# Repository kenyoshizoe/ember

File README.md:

# Ember
## Overview
32Key Hall Effect Keyboard for Gaming.

## Web Configuration Tool

Meet Ember’s control room in the browser. The Next.js‑powered configurator lets you:

- Configuring keymaps with instant write-backs over Web Serial
- Watch real-time hall-effect telemetry and dial in rapid trigger thresholds
- Fire off calibration, DFU, and other maintenance commands in a single click

Launch (Chrome / Edge recommended):
https://ember.kenyo.dev

https://x.com/m3ssy_ken/status/1974076255810269626

## PCB
pcb/ember

基板はKiCAD7で制作され、USBコネクタを除く全てのパーツはJLCPCBのPCBAサービスで実装することができます。
TypeCコネクタは[5077CR-16-SMC2-BK-TR](https://akizukidenshi.com/catalog/g/gC-14356/)を用いることができます。

pcb was designed with KiCAD 7.
All of components except USB Connector is available at jlcpcb pcba service.

## Case
pcb/ember_bottom_plate, pcb/ember_top_plate

## Communication
このキーボードはHID&CDC複合デバイスとして認識されます。
各種設定はCDCから行うことができます。

This keyboard is recognized as HID&CDC composite device.
Configuration (Keymapping, Calibration, Rapid Trigger, etc...) can be done from CDC.

### Packet Structure
Query (Read)
| Bytes     | Description |
| --------- | ----------- |
| 0x00      | 0           |
| 0x01~0x02 | Address     |
| 0x03      | Length      |

Response (Read)
| Bytes           | Description        |
| --------------- | ------------------ |
| 0x00            | Success=0 Failed=1 |
| 0x01~0x02       | Address            |
| 0x03            | Length             |
| 0x04~(Length+4) | Data               |

Query (Write)
| Bytes           | Description |
| --------------- | ----------- |
| 0x00            | 1           |
| 0x01~0x02       | Address     |
| 0x03            | Length      |
| 0x04~(Length+4) | Data        |

Response (Write)
| Bytes     | Description        |
| --------- | ------------------ |
| 0x00      | Success=0 Failed=1 |
| 0x01~0x02 | Address            |
| 0x03      | Length             |

これらのクエリ/レスポンスをCOBSを用いてエンコード/デコードしてから送受信します。
Send these query with encoding/decoding with COBS.

### Address Map
| Address       | Description                                        | W/R |
| ------------- | -------------------------------------------------- | --- |
| 0x0000-0x0004 | Key0 Config                                        | W/R |
| 0x0005-0x0009 | Key1 Config                                        | W/R |
| 0x000A-0x000E | Key2 Config                                        | W/R |
| ...           | ...                                                | ... |
| 0x009B-0x009F | Key31 Config                                       | W/R |
| 0x00A0-0x00FF | Reserved                                           | -   |
| 0x0100        | Key1 MIDI Note Number                              | W/R |
| 0x0101        | Key2 MIDI Note Number                              | W/R |
| 0x0102        | Key3 MIDI Note Number                              | W/R |
| ...           | ...                                                | ... |
| 0x0120-0x0FFF | Reserved                                           | -   |
| 0x1000-0x1003 | Key0 Calibaration Data                             | R   |
| 0x1004-0x1007 | Key1 Calibaration Data                             | R   |
| ...           | ...                                                | ... |
| 0x107B-0x107F | Key31 Calibration Data                             | R   |
| 0x1080-0x1FFF | Reserved                                           | -   |
| 0x2000        | Key0 Push distance                                 | R   |
| 0x2001        | Key1 Push distance                                 | R   |
| ...           | ...                                                | ... |
| 0x201F        | Key31 Push distance                                | R   |
| 0x2020-0x2FFF | Reserved                                           | -   |
| 0x3000        | Save Config                                        | W   |
| 0x3001        | Calibration (0=Disable 1=Enable)                   | W   |
| 0x3002        | Reset Config to default                            | W   |
| 0x3003        | Reset MCU                                          | W   |
| 0x3004        | Enter DFU                                          | W   |
| 0x3005-0xFFFF | Reserved                                           | -   |
| 0x4000        | Mode (0=DISABLED, 1=CALIBRATE, 2=KEYBAORD, 3=MIDI) | W/R |

それぞれのキーの設定は次のようになっています。
Each key config is as follows:
| Address | Description                                                      |
| ------- | ---------------------------------------------------------------- |
| 0x00    | key_code                                                         |
| 0x01    | key_type (0=DISABLED, 1=CALIBRATE, 2=THRESHOLD, 3=RAPID_TRIGGER) |
| 0x02    | actuation_point (0.1mm unit)                                     |
| 0x03    | rappid_trigger_up_sensivity                                      |
| 0x04    | rappid_trigger_down_sensivity                                    |

それぞれのキーのキャリブレーションデータは以下のようになっています。
Each key calibration data is as follows:
| Address   | Description |
| --------- | ----------- |
| 0x00~0x01 | max_value   |
| 0x02~0x03 | min_value   |

## License

Unless otherwise noted, all original content in this repository—including the
firmware, web configurator, scripts, PCB design files, schematics, and case
design files—is licensed under the [MIT License](LICENSE).

This includes permission to use the design files to manufacture, distribute,
and sell physical products based on those designs.

Third-party components remain subject to their respective licenses.

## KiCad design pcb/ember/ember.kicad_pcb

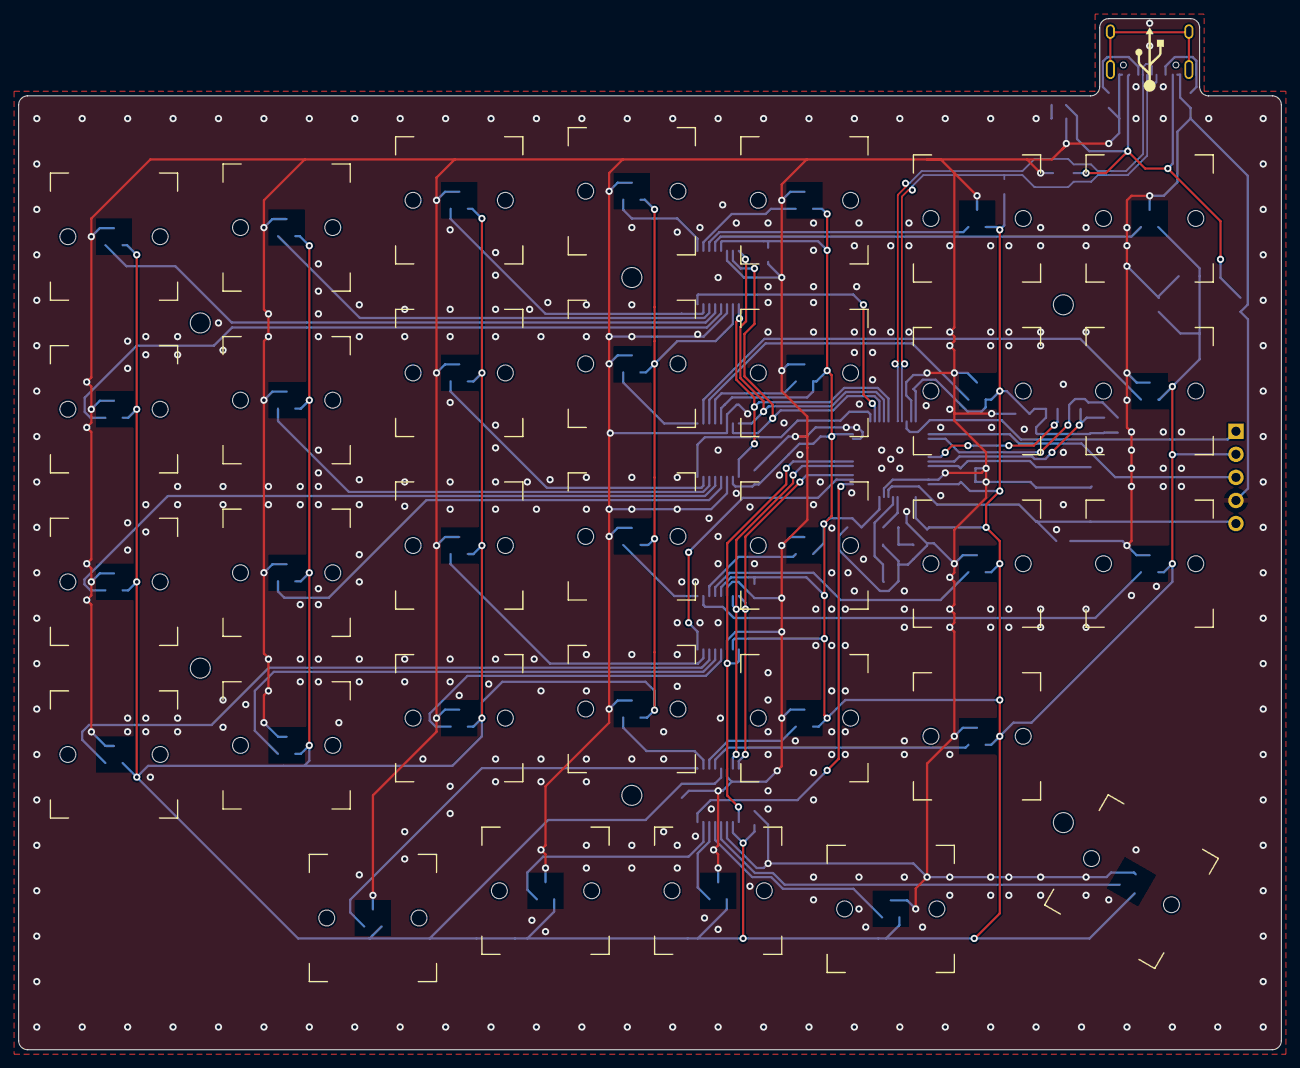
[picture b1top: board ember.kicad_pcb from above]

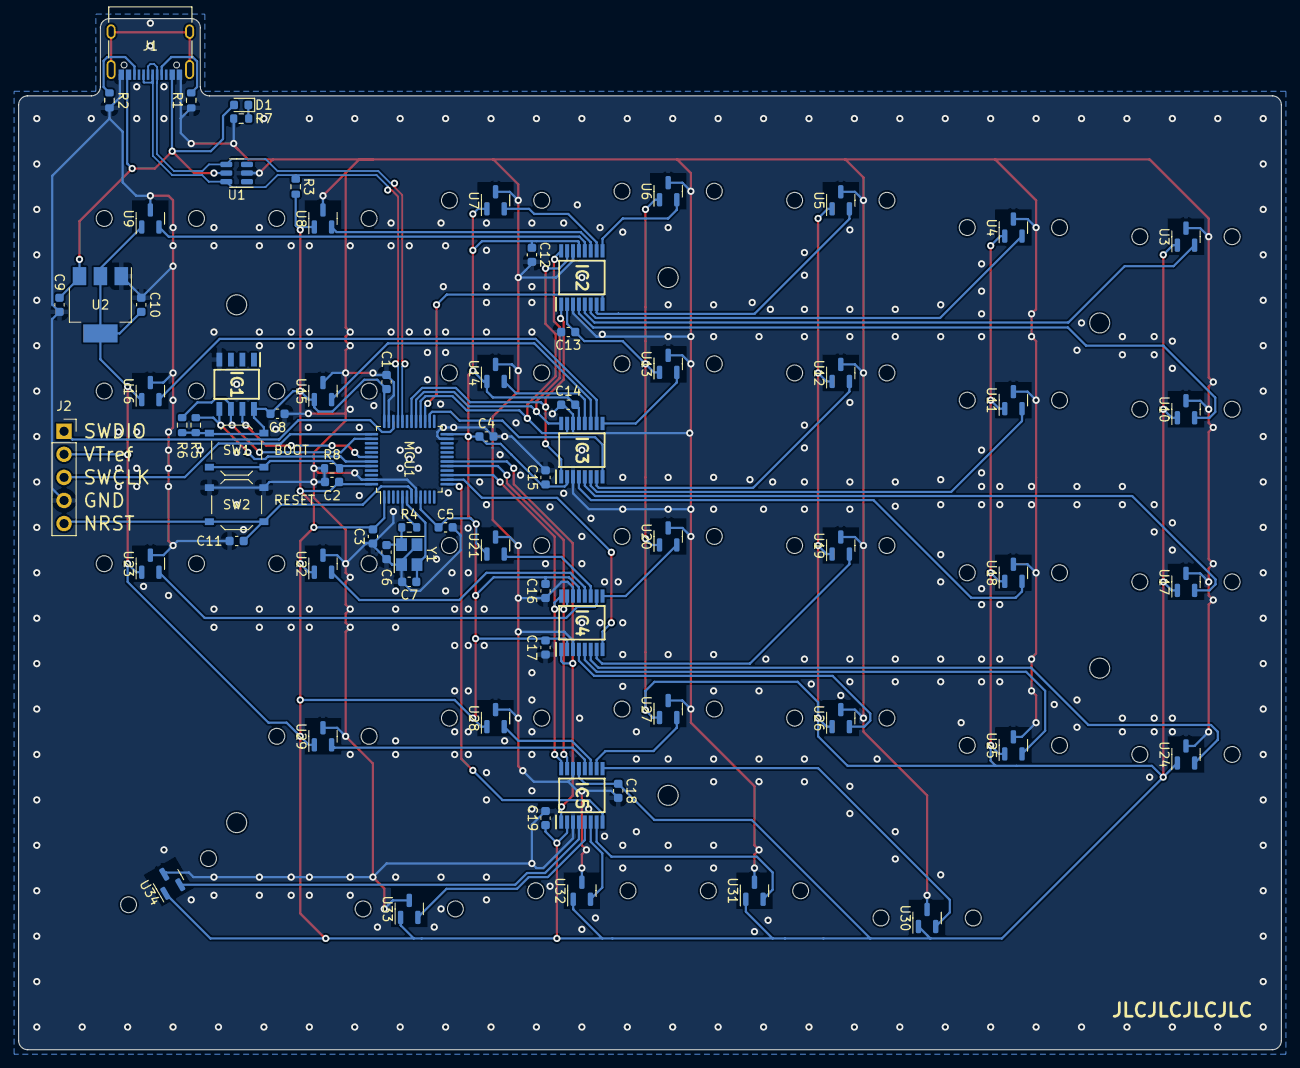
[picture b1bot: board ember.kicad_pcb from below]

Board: 2 copper layers, 139.0 x 113.5 mm, 111 parts (73 on the bottom side), 60 nets.

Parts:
C1, C2, C3, C4, C8, C11, C12, C13, C14, C15, C16, C17, C18, C19: 100n; C_0603_1608Metric
C5: 10n; C_0603_1608Metric
C6, C7: 10p; C_0603_1608Metric
C9: 10u; C_0603_1608Metric
C10: 22u; C_0603_1608Metric
D1: LED; LED_0603_1608Metric
H1, H2, H3, H4, H5, H6: MountingHole; MountingHole_2.2mm_M2
H7, H8, H9, H10, H11, H12, H13, H14, H15, H16, H17, H18, H19, H20, H21, H22, H23, H24, H25, H26, H27, H28, H29, H30, H31, H32, H33, H34, H35, H36, H37, H38: KeySwitch; MX-1U-NoPins
IC1: M24C64-RMN6TP; SOIC127P600X175-8N
IC2, IC3, IC4, IC5: ADG708BRUZ-REEL7; SOP65P640X120-16N
J1: USB_C_Receptacle_USB2.0; USB_C_Receptacle_XKB_U262-16XN-4BVC11
J2: Conn_01x05_Socket; PinSocket_1x05_P2.54mm_Vertical
MCU1: STM32F303CBTx; LQFP-48_7x7mm_P0.5mm
R1, R2: 5.1k; R_0603_1608Metric
R3: 1.5k; R_0603_1608Metric
R4, R8: 1k; R_0603_1608Metric
R5, R6: 10k; R_0603_1608Metric
R7: 470; R_0603_1608Metric
SW1: BOOT; SW_Push_1P1T_XKB_TS-1187A
SW2: RESET; SW_Push_1P1T_XKB_TS-1187A
U1: SRV05-4; SOT-23-6
U2: AMS1117-3.3; SOT-223-3_TabPin2
U3, U4, U5, U6, U7, U8, U9, U10, U11, U12, U13, U14, U15, U16, U17, U18, U19, U20, U21, U22, U23, U24, U25, U26, U27, U28, U29, U30, U31, U32, U33, U34: Hall_Sensor; SOT-23
Y1: 16MHz; Crystal_SMD_3225-4Pin_3.2x2.5mm

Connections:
+3.3V: C1.1, C2.1, C3.1, C4.1, C5.1, C8.1, C10.1, C12.1, C13.1, C14.1, C15.1, C16.1, C17.1, C18.1, C19.1, IC1.8 (VCC), IC2.2 (EN), IC2.13 (VDD), IC3.2 (EN), IC3.13 (VDD), IC4.2 (EN), IC4.13 (VDD), IC5.2 (EN), IC5.13 (VDD), J2.2, MCU1.1 (VBAT), MCU1.9 (VDDA), MCU1.24 (VDD), MCU1.36 (VDD), MCU1.48 (VDD), R3.2, R5.1, R6.1, SW1.2, U2.2 (VO), U3.1 (VDD), U4.1 (VDD), U5.1 (VDD), U6.1 (VDD), U7.1 (VDD), U8.1 (VDD), U9.1 (VDD), U10.1 (VDD), U11.1 (VDD), U12.1 (VDD), U13.1 (VDD), U14.1 (VDD), U15.1 (VDD), U16.1 (VDD), U17.1 (VDD), U18.1 (VDD), U19.1 (VDD), U20.1 (VDD), U21.1 (VDD), U22.1 (VDD), U23.1 (VDD), U24.1 (VDD), U25.1 (VDD), U26.1 (VDD), U27.1 (VDD), U28.1 (VDD), U29.1 (VDD), U30.1 (VDD), U31.1 (VDD), U32.1 (VDD), U33.1 (VDD), U34.1 (VDD)
+5V: C9.1, D1.2 (A), J1.A4 (VBUS), J1.A9 (VBUS), J1.B4 (VBUS), J1.B9 (VBUS), U1.5 (VP), U2.3 (VI)
ADC1: IC5.8 (D), MCU1.13 (PA3)
ADC2: IC4.8 (D), MCU1.14 (PA4)
ADC3: IC3.8 (D), MCU1.26 (PB13)
ADC4: IC2.8 (D), MCU1.27 (PB14)
BOOT: MCU1.44 (BOOT0), R8.1, SW1.1
GND: C1.2, C2.2, C3.2, C4.2, C5.2, C6.2, C7.2, C8.2, C9.2, C10.2, C11.2, C12.2, C13.2, C14.2, C15.2, C16.2, C17.2, C18.2, C19.2, IC1.4 (VSS), IC2.3 (VSS), IC2.14 (GND), IC3.3 (VSS), IC3.14 (GND), IC4.3 (VSS), IC4.14 (GND), IC5.3 (VSS), IC5.14 (GND), J1.A1 (GND), J1.A12 (GND), J1.B1 (GND), J1.B12 (GND), J2.4, MCU1.8 (VSSA), MCU1.23 (VSS), MCU1.35 (VSS), MCU1.47 (VSS), R1.2, R2.2, R7.2, R8.2, SW2.2, U1.2 (VN), U2.1 (GND), U3.3 (GND), U4.3 (GND), U5.3 (GND), U6.3 (GND), U7.3 (GND), U8.3 (GND), U9.3 (GND), U10.3 (GND), U11.3 (GND), U12.3 (GND), U13.3 (GND), U14.3 (GND), U15.3 (GND), U16.3 (GND), U17.3 (GND), U18.3 (GND), U19.3 (GND), U20.3 (GND), U21.3 (GND), U22.3 (GND), U23.3 (GND), U24.3 (GND), U25.3 (GND), U26.3 (GND), U27.3 (GND), U28.3 (GND), U29.3 (GND), U30.3 (GND), U31.3 (GND), U32.3 (GND), U33.3 (GND), U34.3 (GND), Y1.2, Y1.4
MUX1_A: IC4.1 (A0), IC5.1 (A0), MCU1.18 (PB0)
MUX1_B: IC4.16 (A1), IC5.16 (A1), MCU1.15 (PA5)
MUX1_C: IC4.15 (A2), IC5.15 (A2), MCU1.17 (PA7)
MUX2_A: IC2.1 (A0), IC3.1 (A0), MCU1.30 (PA9)
MUX2_B: IC2.16 (A1), IC3.16 (A1), MCU1.29 (PA8)
MUX2_C: IC2.15 (A2), IC3.15 (A2), MCU1.28 (PB15)
NRST: C11.1, J2.5, MCU1.7 (NRST), SW2.1
unnamed: C6.1, R4.1, Y1.1
unnamed: D1.1 (K), R7.1
unnamed: J1.A5 (CC1), R1.1
unnamed: J1.B5 (CC2), R2.1
RCC_OSC_IN: MCU1.5 (PF0), R4.2
RCC_OSC_OUT: C7.1, MCU1.6 (PF1), Y1.3
SCL: IC1.6 (SCL), MCU1.38 (PA15), R6.2
SDA: IC1.5 (SDA), MCU1.43 (PB7), R5.2
SENS_A_S1: IC2.4 (S1), U10.2 (OUT)
SENS_A_S2: IC2.5 (S2), U3.2 (OUT)
SENS_A_S3: IC2.6 (S3), U4.2 (OUT)
SENS_A_S4: IC2.7 (S4), U5.2 (OUT)
SENS_A_S5: IC2.12 (S5), U9.2 (OUT)
SENS_A_S6: IC2.11 (S6), U8.2 (OUT)
SENS_A_S7: IC2.10 (S7), U7.2 (OUT)
SENS_A_S8: IC2.9 (S8), U6.2 (OUT)
SENS_B_S1: IC3.4 (S1), U18.2 (OUT)
SENS_B_S2: IC3.5 (S2), U17.2 (OUT)
SENS_B_S3: IC3.6 (S3), U11.2 (OUT)
SENS_B_S4: IC3.7 (S4), U12.2 (OUT)
SENS_B_S5: IC3.12 (S5), U14.2 (OUT)
SENS_B_S6: IC3.11 (S6), U15.2 (OUT)
SENS_B_S7: IC3.10 (S7), U16.2 (OUT)
SENS_B_S8: IC3.9 (S8), U13.2 (OUT)
SENS_C_S1: IC4.4 (S1), U26.2 (OUT)
SENS_C_S2: IC4.5 (S2), U25.2 (OUT)
SENS_C_S3: IC4.6 (S3), U24.2 (OUT)
SENS_C_S4: IC4.7 (S4), U19.2 (OUT)
SENS_C_S5: IC4.12 (S5), U22.2 (OUT)
SENS_C_S6: IC4.11 (S6), U21.2 (OUT)
SENS_C_S7: IC4.10 (S7), U23.2 (OUT)
SENS_C_S8: IC4.9 (S8), U20.2 (OUT)
SENS_D_S1: IC5.4 (S1), U34.2 (OUT)
SENS_D_S2: IC5.5 (S2), U33.2 (OUT)
SENS_D_S3: IC5.6 (S3), U32.2 (OUT)
SENS_D_S4: IC5.7 (S4), U31.2 (OUT)
SENS_D_S5: IC5.12 (S5), U29.2 (OUT)
SENS_D_S6: IC5.11 (S6), U28.2 (OUT)
SENS_D_S7: IC5.10 (S7), U27.2 (OUT)
SENS_D_S8: IC5.9 (S8), U30.2 (OUT)
SWCLK: J2.3, MCU1.37 (PA14)
SWDIO: J2.1, MCU1.34 (PA13)
USB_D+: J1.A6 (D+), J1.B6 (D+), MCU1.33 (PA12), R3.1, U1.6 (IO4)
USB_D-: J1.A7 (D-), J1.B7 (D-), MCU1.32 (PA11), U1.4 (IO3)
WC: IC1.7 (~WC), MCU1.42 (PB6)

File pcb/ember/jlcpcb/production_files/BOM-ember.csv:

Comment,Designator,Footprint,LCSC
STM32F303CBTx,MCU1,LQFP-48_7x7mm_P0.5mm,C108516
16MHz,Y1,Crystal_SMD_3225-4Pin_3.2x2.5mm,C13738
100n,"C1,C11,C12,C13,C14,C15,C16,C17,C18,C19,C2,C3,C4,C8",C_0603_1608Metric,C14663
10p,"C6,C7",C_0603_1608Metric,C1634
10u,C9,C_0603_1608Metric,C19702
1k,"R4,R8",R_0603_1608Metric,C21190
1.5k,R3,R_0603_1608Metric,C22843
470,R7,R_0603_1608Metric,C23179
5.1k,"R1,R2",R_0603_1608Metric,C23186
10k,"R5,R6",R_0603_1608Metric,C25804
Hall_Sensor,"U10,U11,U12,U13,U14,U15,U16,U17,U18,U19,U20,U21,U22,U23,U24,U25,U26,U27,U28,U29,U3,U30,U31,U32,U33,U34,U4,U5,U6,U7,U8,U9",SOT-23,C2904393
BOOT,"SW1,SW2",SW_Push_1P1T_XKB_TS-1187A,C318884
USB_C_Receptacle_USB2.0,J1,USB_C_Receptacle_XKB_U262-16XN-4BVC11,C319148
ADG708BRUZ-REEL7,"IC2,IC3,IC4,IC5",SOP65P640X120-16N,C35325
10n,C5,C_0603_1608Metric,C57112
22u,C10,C_0603_1608Metric,C59461
AMS1117-3.3,U2,SOT-223-3_TabPin2,C6186
LED,D1,LED_0603_1608Metric,C72043
M24C64-RMN6TP,IC1,SOIC127P600X175-8N,C79988
SRV05-4,U1,SOT-23-6,C85364
KeySwitch,H29,MX-1U-NoPins,
KeySwitch,H17,MX-1U-NoPins,
MountingHole,H3,MountingHole_2.2mm_M2,
KeySwitch,H20,MX-1U-NoPins,
MountingHole,H2,MountingHole_2.2mm_M2,
KeySwitch,H31,MX-1U-NoPins,
KeySwitch,H11,MX-1U-NoPins,
KeySwitch,H19,MX-1U-NoPins,
KeySwitch,H9,MX-1U-NoPins,
KeySwitch,H24,MX-1U-NoPins,
KeySwitch,H21,MX-1U-NoPins,
MountingHole,H1,MountingHole_2.2mm_M2,
KeySwitch,H23,MX-1U-NoPins,
KeySwitch,H10,MX-1U-NoPins,
KeySwitch,H14,MX-1U-NoPins,
KeySwitch,H32,MX-1U-NoPins,
MountingHole,H5,MountingHole_2.2mm_M2,
KeySwitch,H16,MX-1U-NoPins,
KeySwitch,H7,MX-1U-NoPins,
KeySwitch,H13,MX-1U-NoPins,
KeySwitch,H30,MX-1U-NoPins,
KeySwitch,H8,MX-1U-NoPins,
KeySwitch,H15,MX-1U-NoPins,
KeySwitch,H18,MX-1U-NoPins,
KeySwitch,H25,MX-1U-NoPins,
KeySwitch,H26,MX-1U-NoPins,
KeySwitch,H12,MX-1U-NoPins,
MountingHole,H6,MountingHole_2.2mm_M2,
KeySwitch,H27,MX-1U-NoPins,
KeySwitch,H28,MX-1U-NoPins,
MountingHole,H4,MountingHole_2.2mm_M2,
KeySwitch,H22,MX-1U-NoPins,
Conn_01x05_Socket,J2,PinSocket_1x05_P2.54mm_Vertical,
KeySwitch,H38,MX-1U-NoPins,
KeySwitch,H37,MX-1U-NoPins,
KeySwitch,H36,MX-1U-NoPins,
KeySwitch,H35,MX-1U-NoPins,
KeySwitch,H34,MX-1U-NoPins,
KeySwitch,H33,MX-1U-NoPins,

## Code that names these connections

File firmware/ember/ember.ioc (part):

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Mcu.Name=STM32F303C(B-C)Tx
Mcu.Package=LQFP48
Mcu.UserName=STM32F303CBTx
PA11.Mode=Device
PA11.Signal=USB_DM
PA12.Mode=Device
PA12.Signal=USB_DP
PA13.Mode=Serial_Wire
PA13.Signal=SYS_JTMS-SWDIO
PA14.Mode=Serial_Wire
PA14.Signal=SYS_JTCK-SWCLK
PA15.Mode=I2C
PA15.Signal=I2C1_SCL
PA3.Mode=IN4-Single-Ended
PA3.Signal=ADC1_IN4
PA4.Mode=IN1-Single-Ended
PA4.Signal=ADC2_IN1
PA5.GPIOParameters=GPIO_Speed,GPIO_Label
PA5.GPIO_Label=MUX1_B
PA5.GPIO_Speed=GPIO_SPEED_FREQ_HIGH
PA5.Signal=GPIO_Output
PA7.GPIOParameters=GPIO_Speed,GPIO_Label
PA7.GPIO_Label=MUX1_C
PA7.GPIO_Speed=GPIO_SPEED_FREQ_HIGH
PA7.Signal=GPIO_Output
PA8.GPIOParameters=GPIO_Speed,GPIO_Label
PA8.GPIO_Label=MUX2_B
PA8.GPIO_Speed=GPIO_SPEED_FREQ_HIGH
PA8.Signal=GPIO_Output
PA9.GPIOParameters=GPIO_Speed,GPIO_Label
PA9.GPIO_Label=MUX2_A
PA9.GPIO_Speed=GPIO_SPEED_FREQ_HIGH
PA9.Signal=GPIO_Output
PB0.GPIOParameters=GPIO_Speed,GPIO_Label
PB0.GPIO_Label=MUX1_A
PB0.GPIO_Speed=GPIO_SPEED_FREQ_HIGH
PB0.Signal=GPIO_Output
PB13.Mode=IN5-Single-Ended
PB13.Signal=ADC3_IN5
PB14.Mode=IN4-Single-Ended
PB14.Signal=ADC4_IN4
PB15.GPIOParameters=GPIO_Speed,GPIO_Label
PB15.GPIO_Label=MUX2_C
PB15.GPIO_Speed=GPIO_SPEED_FREQ_HIGH
PB15.Signal=GPIO_Output
PB6.GPIOParameters=GPIO_Label
PB6.GPIO_Label=EEPROM_WC
PB6.Signal=GPIO_Output
PB7.Mode=I2C
PB7.Signal=I2C1_SDA
PF0-OSC_IN.Mode=HSE-External-Oscillator
PF0-OSC_IN.Signal=RCC_OSC_IN
PF1-OSC_OUT.Mode=HSE-External-Oscillator
PF1-OSC_OUT.Signal=RCC_OSC_OUT
RCC.HSEPLLFreq_Value=16000000
RCC.HSE_VALUE=16000000
RCC.SYSCLKFreq_VALUE=16000000
RCC.SYSCLKSourceVirtual=RCC_SYSCLKSOURCE_HSE
board=custom

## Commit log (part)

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2023-08-13 :tada: add pcb design
2023-08-13 :wrench: add .gitignore for kicad
2023-08-14 :tada: generate project
2023-08-14 :sparkles: add class for cb4051b
2023-08-14 :sparkles: add c_cpp_properties
2023-08-14 :recycle: entry_point->app
2023-08-14 :bug: fix cb4051b ch_
2023-08-14 :sparkles: add NextCh()
2023-08-14 :sparkles: add CD4051B instance
2023-08-14 :wrench: change adc settings
2023-08-15 :heavy_plus_sign: add tinyusb as submodule
2023-08-15 :wrench: disable USB_DEVICE
2023-08-15 :sparkles: configure makefile to build tinyUSB
2023-08-15 :wrench: enable usb irq
2023-08-15 :sparkles: add tusb_config.h
2023-08-23 :wrench: ver1.1
2023-08-23 :sparkles: add tusb process
2023-08-23 :sparkles: add eeprom
2023-08-23 :wrench: fix tinyusb include in makefile
2023-08-24 :wrench: change usb irq setting
2023-08-24 :heavy_plus_sign: add segger_rtt
2023-08-24 :wrench: configure usb_descriptor/tusb_config
2023-08-24 :sparkles: include segger rtt
2023-08-24 :sparkles: add tusb cdc & hid process
2023-08-24 :sparkles: change hid desc
2023-08-24 :sparkles: clean app
2023-08-24 :bug: add 1.5k pullup to D+
2023-08-24 :wrench: add VTref Pin
2023-08-25 :sparkles: all key adc
2023-08-25 :sparkles: adc all kyes @ 800Hz
2023-08-25 :sparkles: change tim hz
2023-08-25 :tada: add keyboard class
2023-08-25 :tada: add keyswitch class
2023-08-25 :sparkles: add keycodes
2023-08-25 :tada: simple keyboard app
2023-08-26 :sparkles: change adc sampling time
2023-08-26 :sparkles: change gpio speed
2023-08-27 change hall size 3.5mm→2.2mm(M2)
2023-08-27 :sparkles: change usb connector position
2023-08-28 :sparkles: replace cd4052->ad708
2023-08-28 :sparkles: add 3d data
2023-08-28 :sparkles: add bypass cap
2023-08-29 :sparkles: add config.h
2023-08-29 :sparkles: change constructor / getter
2023-08-29 :tada: add flash class
2023-08-29 :sparkles: add load flash process
2023-08-29 :sparkles: move SetADCValue
2023-08-29 :sparkles: change end calibration process
2023-08-29 :wastebasket: reduce setup print
2023-08-29 :sparkles: add DATA memory area
2023-08-31 :sparkles: opampを使ってのADCに切り替えられるようにピンアサインを変更
2023-09-02 :sparkles: add pcb plates
2023-09-02 :sparkles: add usb logo
2023-09-02 :sparkles: export production files
2023-09-02 :tada: add ADCValToDistance
2023-09-02 :sparkles: add GetLastPosition()
2023-09-02 :sparkles: change config
2023-09-02 :bug: fix actuation condition
2023-09-02 :tada: add rappid trigger class
2023-09-13 :wrench: change cubemx pin assign
2023-09-13 :sparkles: change Keyboard::ChToIndex() for new map
2023-09-13 :rocket: polling rate 500Hz
2023-09-14 :sparkles: split amux process
2023-09-14 :sparkles: add CD4051B::Init()
2023-09-14 :wrench: change amux ptr->GlobalVariable
2023-09-14 :wrench: change config data structure
2023-09-14 :wrench: make Flash::GetDefaultConfig public
2023-09-14 :sparkles: add cobs.h
2023-09-14 :tada: add configrator
2023-09-14 :memo: add readme
2023-09-16 :wrench: change hz 500->250
2023-09-16 :sparkles: change default settings
2023-09-16 :bug: fix referrence
2023-09-16 :bug: add setkeyboard/setconfig
2023-09-16 :bug: fix config address
2023-09-16 :wrench: add check data length process
2023-09-16 :bug: fix Keyboard::Keyboard constructor
2023-09-16 :bug: add delimiter to response
2023-09-16 :bug: fix data address
2023-09-16 :wrench: add save config address
2023-09-16 :tada: add python scripts to test configurator
2023-09-16 :sparkles: change script permission
2023-09-16 :sparkles: implement enter dfu mode
2023-09-16 :sparkles: add script to enter dfu
2023-09-16 :memo: move readme
2023-09-16 :memo: add pcb images to readme
2023-09-16 :bug: fix address check condition
2023-09-16 :sparkles: add response check to scripts
2023-09-16 :memo: fix readme address map
2023-09-18 :sparkles: create next.js project
2023-09-27 🔧 introducing prettier
2023-09-27 🔧 Add .prettierignore
2023-09-27 🎨 applied formatter
2023-09-27 🔧 modified config file
2023-09-27 ⚰️ removed codes and a file no longer needed
2023-09-27 🌱 update html metadata
2023-09-27 🔥 removed files and codes no longer needed
2023-09-27 🔥 removed codes no longer needed.
2023-09-27 💄 add a temporary UI for Configurator
2025-10-03 :heavy_plus_sign: add etl as submodule
2025-10-03 :heavy_plus_sign: update hal version
2025-10-03 :heavy_plus_sign: update tinyusb version
2025-10-03 :wrench: add etl to makefile
2025-10-03 :bug: fix cdc receiving process
2025-10-03 :sparkles: adaptive key_type
2025-10-03 :tada: add Web GUI
2025-10-03 :memo: update readme
2025-10-03 :sparkles: add button to enter-dfu
2025-10-03 fix vercel url
2025-10-03 :sparkles: add web gui img
2025-10-04 :sparkles: add MIDI note selecting drop down box
2025-10-04 :sparkles: add Keyboard Mode Selection
2025-10-04 :sparkles: add MIDI USB EP
2025-10-04 :tada: add DisabledKey, CalibratingKey, Velocity Calucuration, MIDI Mode
2025-10-04 :sparkles: set default key_type THRESHOLD
2025-10-04 :memo: update README about comm protocol
2025-10-04 :bug: fix configurator length
2025-10-04 :sparkles: add manual address control
2025-10-04 :bug: add blank 3bytes to Config for alignment
2025-10-04 :recycle: refactor emberProtocol / useKeboard
2025-10-04 :sparkles: square push distance bar
2025-10-04 :wrench: change control panel layout
2026-02-12 Update README with tweet link and PCB details
    Added a link to a tweet and updated PCB information.
2026-02-28 :bug: minor fixes
2026-04-07 Change launch URL in README
    Updated the launch URL for the application.
